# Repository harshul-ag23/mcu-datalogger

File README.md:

# MCU Data Logger (STM32 + RTC + EEPROM)

## Overview

This project is a microcontroller-based data logger built using STM32, an external RTC (DS1337), and EEPROM (24LC1025).
The system is designed to log time-based data with reliable storage and external interfacing.

---

## Features

* STM32-based embedded system
* External RTC for accurate timekeeping
* EEPROM for persistent data storage
* I2C communication (RTC + EEPROM)
* UART interface for debugging/logging
* SPI/ICSP interface exposed
* Custom 2-layer PCB designed in KiCad

---

## Hardware Design

### Key Design Decisions

* Pull-up resistors used for I2C communication lines
* Separate crystal circuits:

  * 16 MHz for MCU
  * 32.768 kHz for RTC
* Decoupling capacitors placed near each IC
* Reset circuit designed with pull-up resistor
* EEPROM addressing configured for multiple devices

---

## PCB Layout

* 2-layer PCB design
* Ground plane used for improved signal integrity
* Component placement based on signal flow
* Short routing for critical signals (clock, I2C)

---

## Images

### PCB Layout

### 3D View

### Schematic

---

## What I Learned

* Designing complete embedded hardware systems
* PCB routing and layout considerations
* Interfacing peripherals using I2C, SPI, UART
* Importance of grounding, decoupling, and clock design

---

## Future Improvements

* Add SD card for large data logging
* Implement firmware for real-time logging
* Improve PCB layout optimization

---

## Tools Used

* KiCad (Schematic & PCB Design)
* STM32CubeIDE / Keil (Firmware)
* Oscilloscope, Logic Analyzer (Debugging)

---

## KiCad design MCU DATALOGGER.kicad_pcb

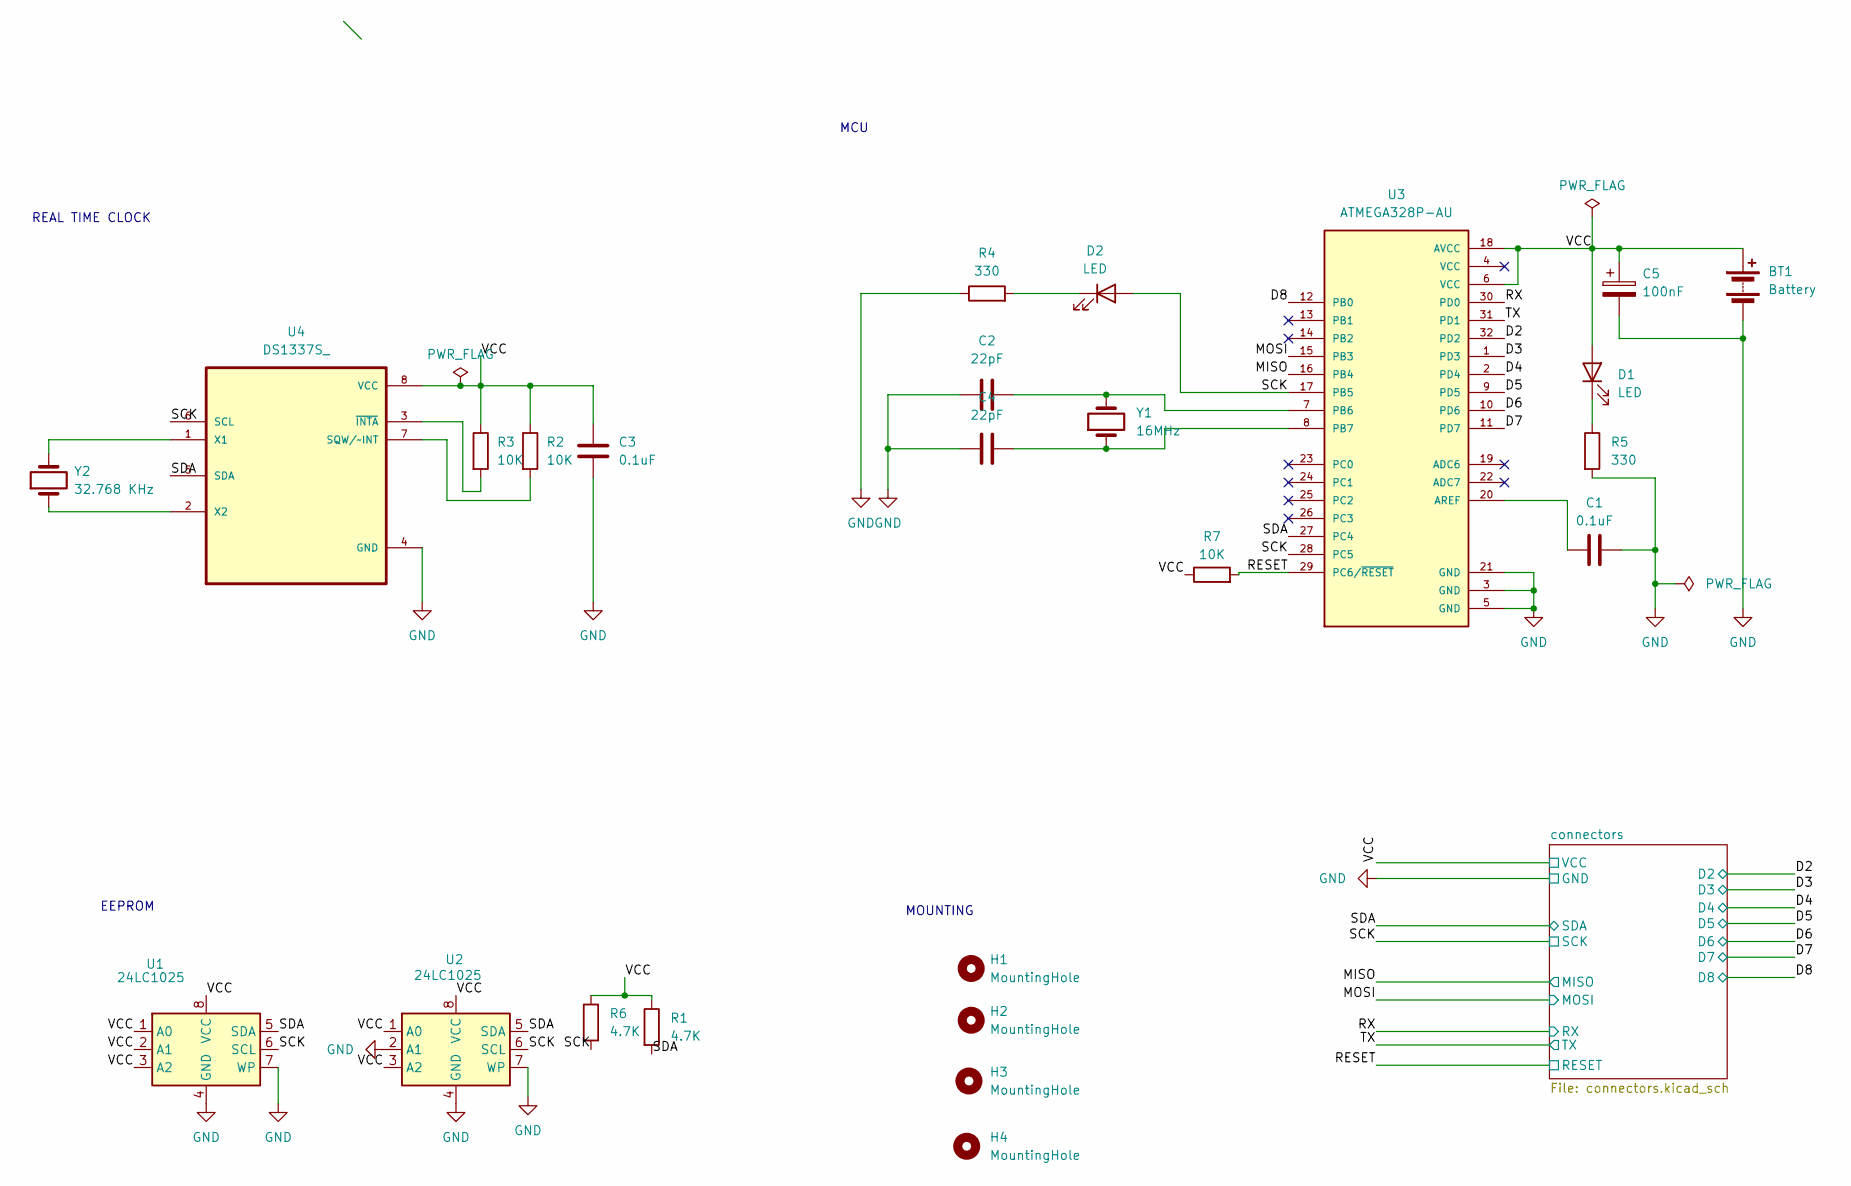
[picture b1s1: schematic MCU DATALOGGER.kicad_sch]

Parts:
BT1: Battery; PinHeader_1x02_P2.54mm_Vertical
C1, C3: 0.1uF; C_0805_2012Metric
C2, C4: 22pF; C_0805_2012Metric
C5: 100nF; C_0805_2012Metric
D1, D2: LED; LED_0805_2012Metric
H1, H2, H3, H4: MountingHole; MountingHole_2.1mm
R1, R6: 4.7K; R_0805_2012Metric
R2, R3, R7: 10K; R_0805_2012Metric
R4, R5: 330; R_0805_2012Metric
U1, U2: 24LC1025; SOIC-8_5.3x5.3mm_P1.27mm
U3: ATMEGA328P-AU; QFP80P900X900X120-32N; PARTREV 8271A
U4: DS1337S_; SOIC127P600X175-8N
Y1: 16MHz; Crystal_SMD_5032-2Pin_5.0x3.2mm_HandSoldering
Y2: 32.768 KHz; Crystal_SMD_5032-2Pin_5.0x3.2mm_HandSoldering

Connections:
/D2: U3.32 (PD2); also elsewhere on the board
/D3: U3.1 (PD3); also elsewhere on the board
/D4: U3.2 (PD4); also elsewhere on the board
/D5: U3.9 (PD5); also elsewhere on the board
/D6: U3.10 (PD6); also elsewhere on the board
/D7: U3.11 (PD7); also elsewhere on the board
/D8: U3.12 (PB0); also elsewhere on the board
/MISO: U3.16 (PB4); also elsewhere on the board
/MOSI: U3.15 (PB3); also elsewhere on the board
/RESET: R7.2, U3.29 (PC6/~RESET); also elsewhere on the board
/RX: U3.30 (PD0); also elsewhere on the board
/SCK: D2.2 (A), R6.2, U1.6 (SCL), U2.6 (SCL), U3.17 (PB5), U3.28 (PC5), U4.6 (SCL); also elsewhere on the board
/SDA: R1.2, U1.5 (SDA), U2.5 (SDA), U3.27 (PC4), U4.5 (SDA); also elsewhere on the board
/TX: U3.31 (PD1); also elsewhere on the board
/VCC: BT1.1 (+), C3.1, C5.1, D1.2 (A), R1.1, R2.1, R3.1, R6.1, R7.1, U1.1 (A0), U1.2 (A1), U1.3 (A2), U1.8 (VCC), U2.1 (A0), U2.3 (A2), U2.8 (VCC), U3.6 (VCC), U3.18 (AVCC), U4.8 (VCC); also elsewhere on the board
GND: BT1.2 (-), C1.2, C2.1, C3.2, C4.1, C5.2, R4.1, R5.2, U1.4 (GND), U1.7 (WP), U2.2 (A1), U2.4 (GND), U2.7 (WP), U3.3 (GND), U3.5 (GND), U3.21 (GND), U4.4 (GND); also elsewhere on the board
unnamed: D1.1 (K), R5.1
unnamed: D2.1 (K), R4.2
unnamed: C1.1, U3.20 (AREF)
unnamed: C2.2, U3.7 (PB6), Y1.2
unnamed: C4.2, U3.8 (PB7), Y1.1
unnamed: R2.2, U4.7 (SQW/~INT)
unnamed: U4.1 (X1), Y2.2
unnamed: U4.2 (X2), Y2.1
unnamed: R3.2, U4.3 (~INTA)

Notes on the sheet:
MOUNTING
REAL TIME CLOCK
EEPROM
MCU

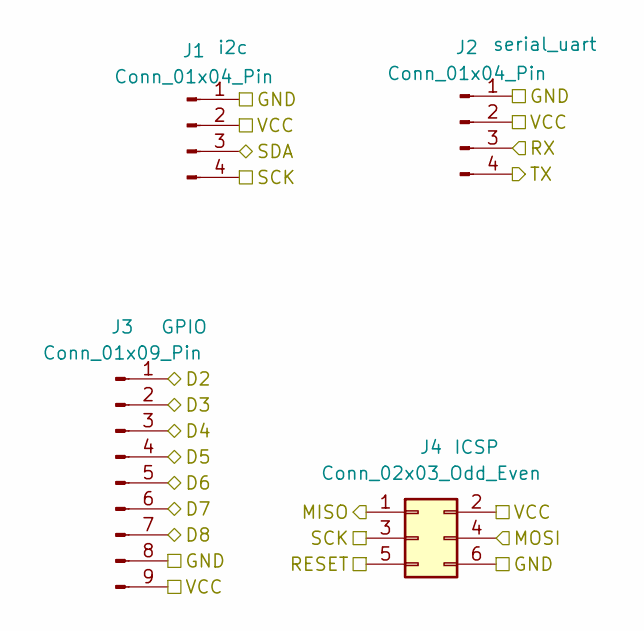
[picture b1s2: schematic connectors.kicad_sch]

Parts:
J1, J2: Conn_01x04_Pin; PinHeader_1x04_P2.54mm_Vertical
J3: Conn_01x09_Pin; PinHeader_1x09_P2.54mm_Vertical
J4: Conn_02x03_Odd_Even; PinHeader_2x03_P2.54mm_Vertical

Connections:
/D2: J3.1; also elsewhere on the board
/D3: J3.2; also elsewhere on the board
/D4: J3.3; also elsewhere on the board
/D5: J3.4; also elsewhere on the board
/D6: J3.5; also elsewhere on the board
/D7: J3.6; also elsewhere on the board
/D8: J3.7; also elsewhere on the board
/MISO: J4.1; also elsewhere on the board
/MOSI: J4.4; also elsewhere on the board
/RESET: J4.5; also elsewhere on the board
/RX: J2.3; also elsewhere on the board
/SCK: J1.4, J4.3; also elsewhere on the board
/SDA: J1.3; also elsewhere on the board
/TX: J2.4; also elsewhere on the board
/VCC: J1.2, J2.2, J3.9, J4.2; also elsewhere on the board
GND: J1.1, J2.1, J3.8, J4.6; also elsewhere on the board

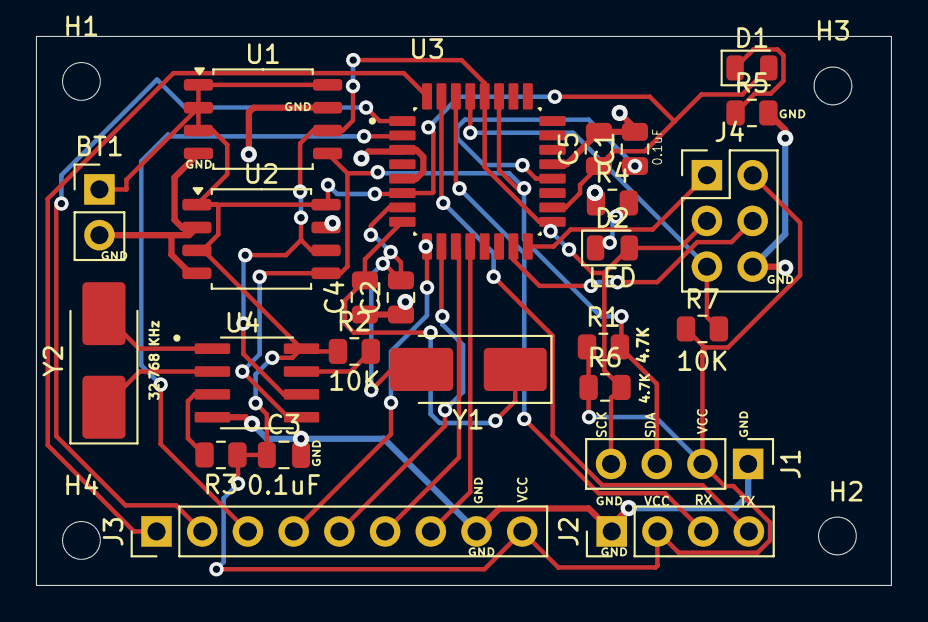
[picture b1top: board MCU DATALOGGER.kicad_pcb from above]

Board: 2 copper layers, 47.5 x 30.5 mm, 29 parts (0 on the bottom side), 25 nets.

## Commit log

2026-05-02 First commit of new project.
2026-05-02 Setup of EEschema for new project
2026-05-03 Have added required symbols to the schematic sheets
2026-05-03 changed the layout and placed symbols according to their places
2026-05-03 added values to symbols
2026-05-03 assigned the footprints
2026-05-03 done wiring of the main sheet
2026-05-03 Completed all the wiring
2026-05-03 Done the final schematic work and net and all
2026-05-05 Done with schematic
2026-05-05 Imported the parts and set the settings
2026-05-05 done the placing
2026-05-05 Done with layout
2026-05-05 Done
2026-05-06 added gerber directories to git ignore
2026-05-06 restructured
2026-05-06 Making final changes
2026-05-06 removed autosaved file
2026-05-06 updated git ignore
2026-05-06 added project images
2026-05-07 some images changes
